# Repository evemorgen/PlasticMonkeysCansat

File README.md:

# Welcome to Plastic Monkeys - Emergency Beacan repo

This is the place where we keep all our work related to Emergency Beacan project.

We are building a CanSat (CanSat is a small soda-sized piece of electronics, created to conduct a scientific mission) equiped with multiple sensors, radio, GPS, thermal camera and screen to provide communication to the victims of natural disasters. Usually, after an earthquake or tsunami, big expeditions and rescue operations take place. Unfortunately they are very often dangerous for rescuers and very expensive. We came up with a solution - instead of people, we can send there many small sats, anyone who finds them can easily send their localization to the rescue center and have a short interview. 

----

## Repo structure

Emergency Beacan is multidisciplinary project involving software, electronics, mechanical design and so on. That being said, there are couple directories covering all mentioned before:

  - [`code`](code/) - keeps all software related stuff
  - [`docs`](docs/) - is the place where we keep project documentation, you might be espetialy interested in our [reports](docs/reports)
  - [`assets`](assets/) - contains all graphical designs regarding our logos and .. assets?
  - [`diagrams`](diagrams/) - all things related to visual representation of conceptual design

----

## Where to find us

We are present in most of modern social media platforms, you can follow us at:
  - our website <http://plastic-monkeys.space>
  - [facebook](https://www.facebook.com/pmcansat/)
  - [instagram](https://www.instagram.com/pmcansat/)
  - [youtube](https://www.youtube.com/channel/UCQk3wuW7xEt5WVLtaiRNTGQ)
  - or write us old fashioned email <hello@plastic-monkeys.space>

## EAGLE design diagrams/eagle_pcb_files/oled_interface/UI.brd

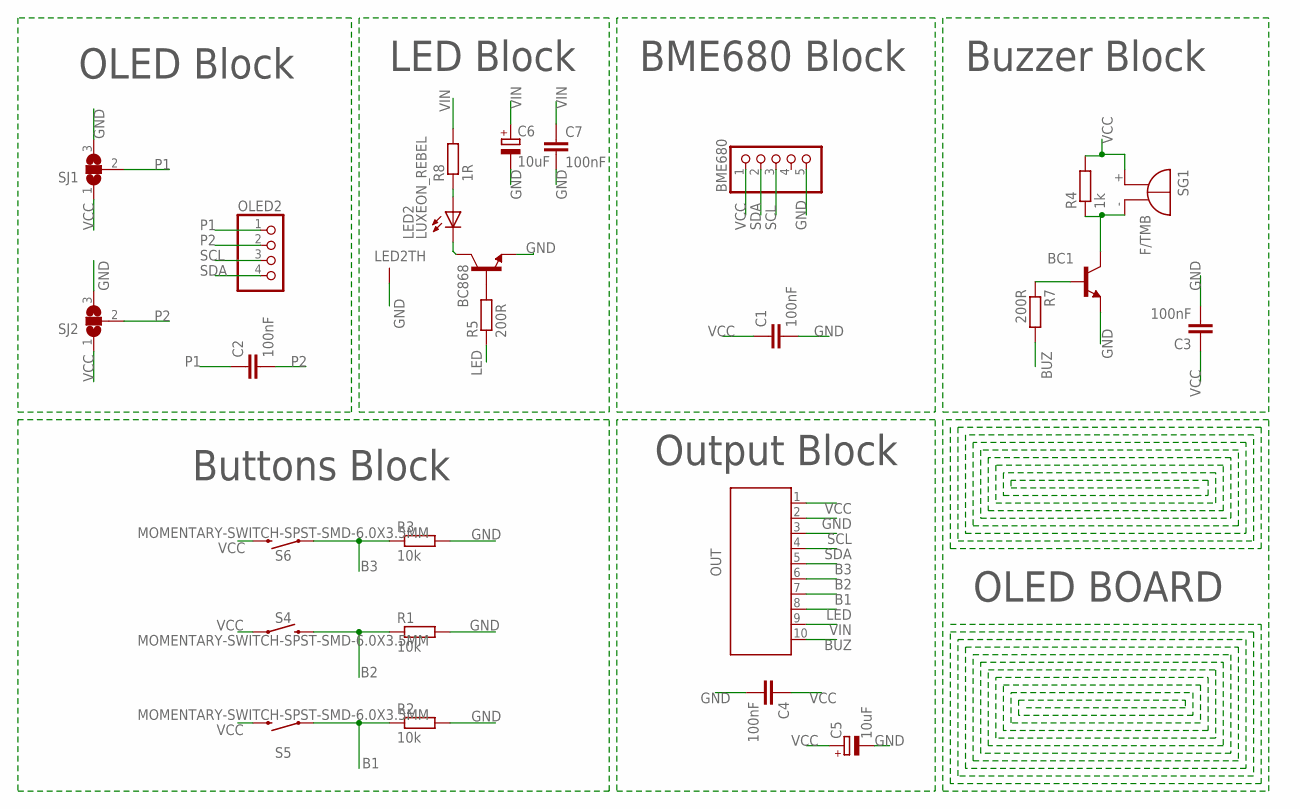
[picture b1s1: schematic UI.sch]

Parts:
BC1, BC868: BC868-NPN-SOT89-BCE; SOT89-BCE
BME680: PINHD-1X5; 1X05
C1, C2, C3, C7: 100nF; C0805
C4: 100nF; C1808
C5, C6: 10uF; SMC_A
LED2: LUXEON_REBEL
OLED2: PINHD-1X4; 1X04
OUT: 686110183422
R1, R2, R3: 10k; M1206
R4: 1k; M0805
R5, R7: 200R; M0805
R8: 1R; R3216
S4, S5, S6: MOMENTARY-SWITCH-SPST-SMD-6.0X3.5MM; TACTILE_SWITCH_SMD_6.0X3.5MM
SG1: F/TMB
SJ1, SJ2: SJ2W; SJ_2

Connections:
B1: OUT.7 (4), R2.1, S5.1
B2: OUT.6 (5), R1.1, S4.2
B3: OUT.5 (6), R3.1, S6.1
BUZ: OUT.10 (1), R7.2
GND: BC1.E, BC868.E, BME680.5, C1.2, C3.2, C4.2, C5.-, C6.-, C7.2, LED2.TH, LED2.TH@1 (TH), LED2.TH@2 (TH), LED2.TH@3 (TH), LED2.TH@4 (TH), OUT.2 (9), R1.2, R2.2, R3.2, SJ1.3, SJ2.3
LED: OUT.8 (3), R5.1
unnamed: LED2.A, LED2.A@1 (A), R8.1
unnamed: BC868.C, LED2.C, LED2.C@1 (C)
unnamed: BC868.B, R5.2
unnamed: BC1.B, R7.1
unnamed: BC1.C, R4.1, SG1.-
P1: C2.1, OLED2.1, SJ1.2
P2: C2.2, OLED2.2, SJ2.2
SCL: BME680.3, OLED2.3, OUT.3 (8)
SDA: BME680.2, OLED2.4, OUT.4 (7)
VCC: BME680.1, C1.1, C3.1, C4.1, C5.+, OUT.1 (10), R4.2, S4.1, S5.2, S6.2, SG1.+, SJ1.1, SJ2.1
VIN: C6.+, C7.1, OUT.9 (2), R8.2

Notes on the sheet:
OLED Block
LED Block
Buttons Block
BME680 Block
Output Block
Buzzer Block
OLED BOARD

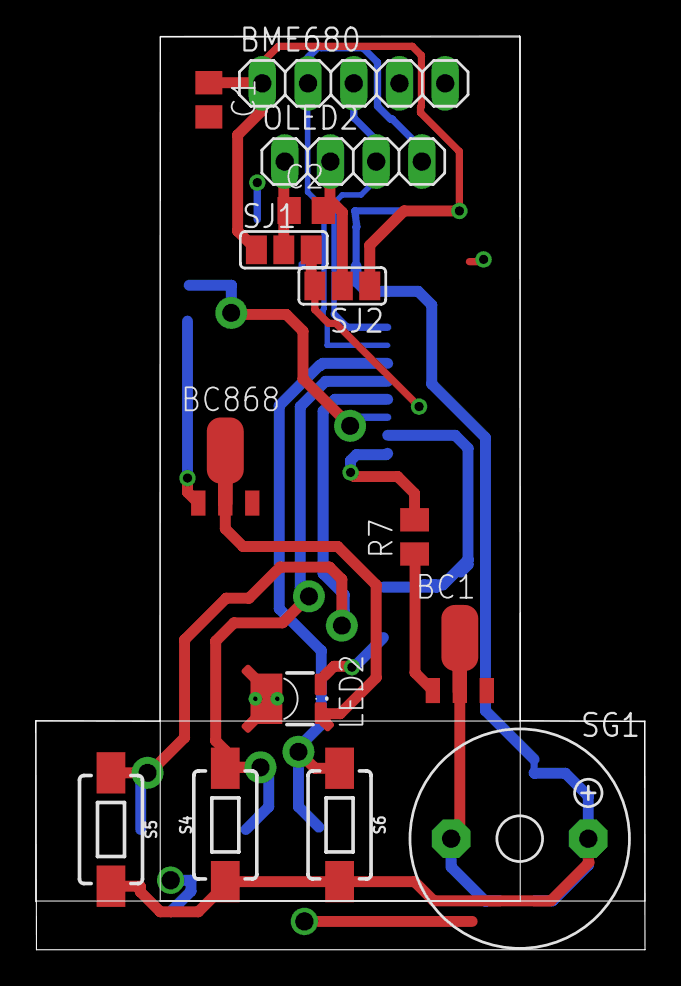
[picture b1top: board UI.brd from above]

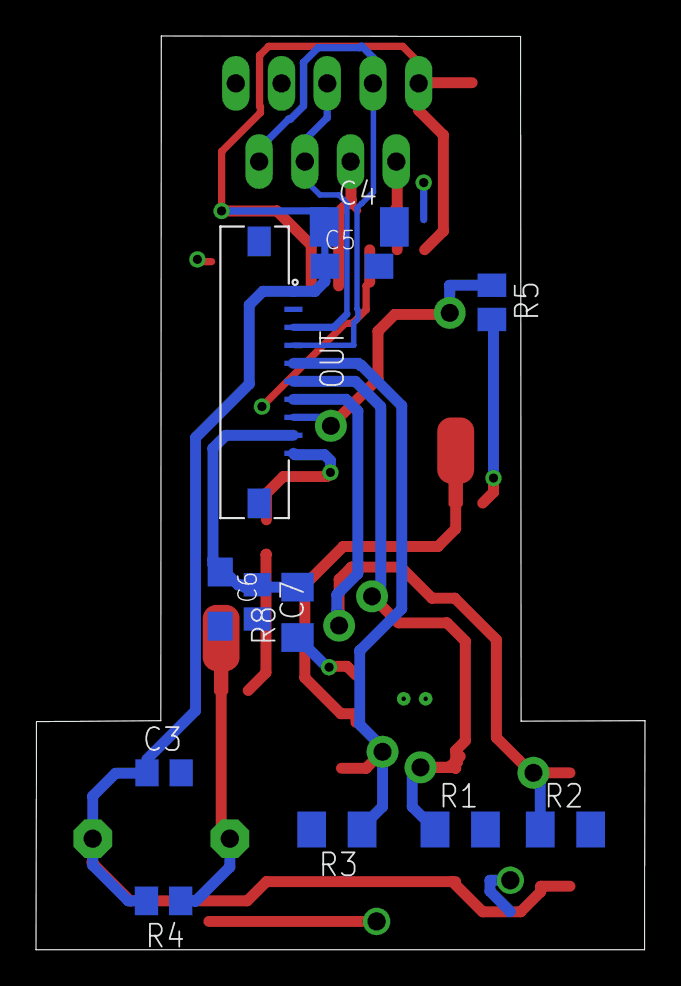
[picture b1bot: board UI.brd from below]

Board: 2 copper layers, 33.8 x 50.8 mm, 26 parts (12 on the bottom side), 17 nets.

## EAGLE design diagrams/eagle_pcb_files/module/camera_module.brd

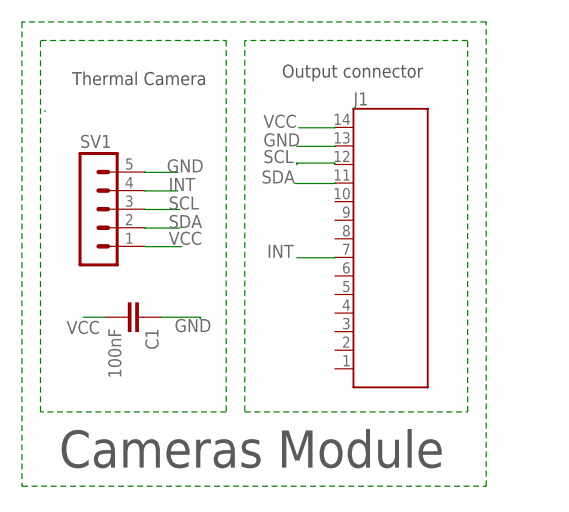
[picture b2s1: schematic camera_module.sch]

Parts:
C1: 100nF; C0805
J1: 686114183522
SV1: MA05-1

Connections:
GND: C1.1, J1.13 (2), SV1.5
INT: J1.7 (8), SV1.4
SCL: J1.12 (3), SV1.3
SDA: J1.11 (4), SV1.2
VCC: C1.2, J1.14 (1), SV1.1

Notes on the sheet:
Thermal Camera
Output connector
Cameras Module

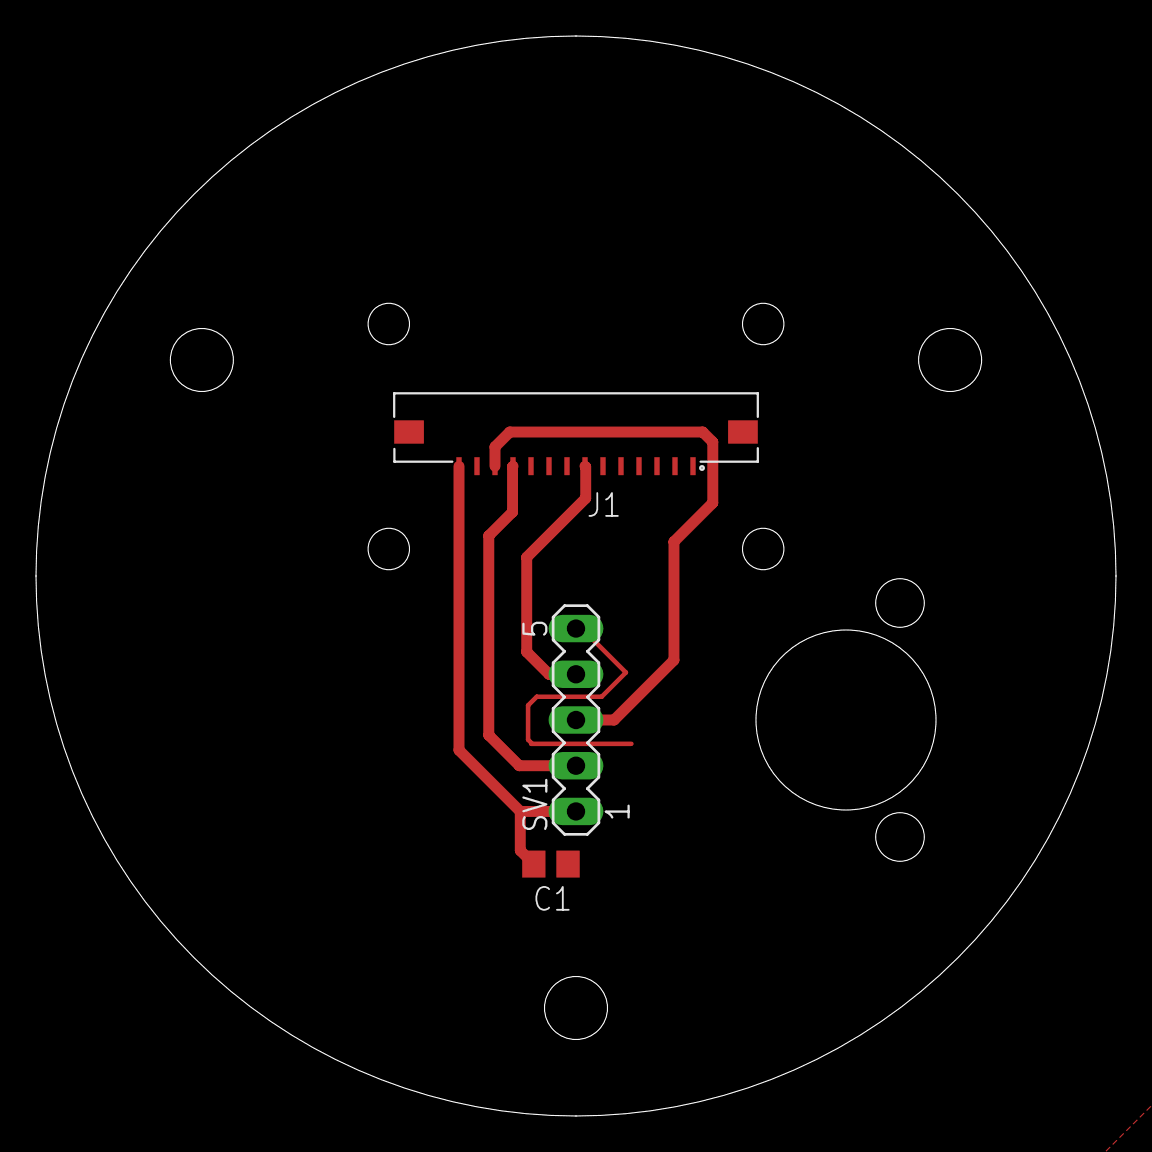
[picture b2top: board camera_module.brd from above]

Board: 2 copper layers, 60.0 x 60.0 mm, 3 parts (0 on the bottom side), 5 nets.

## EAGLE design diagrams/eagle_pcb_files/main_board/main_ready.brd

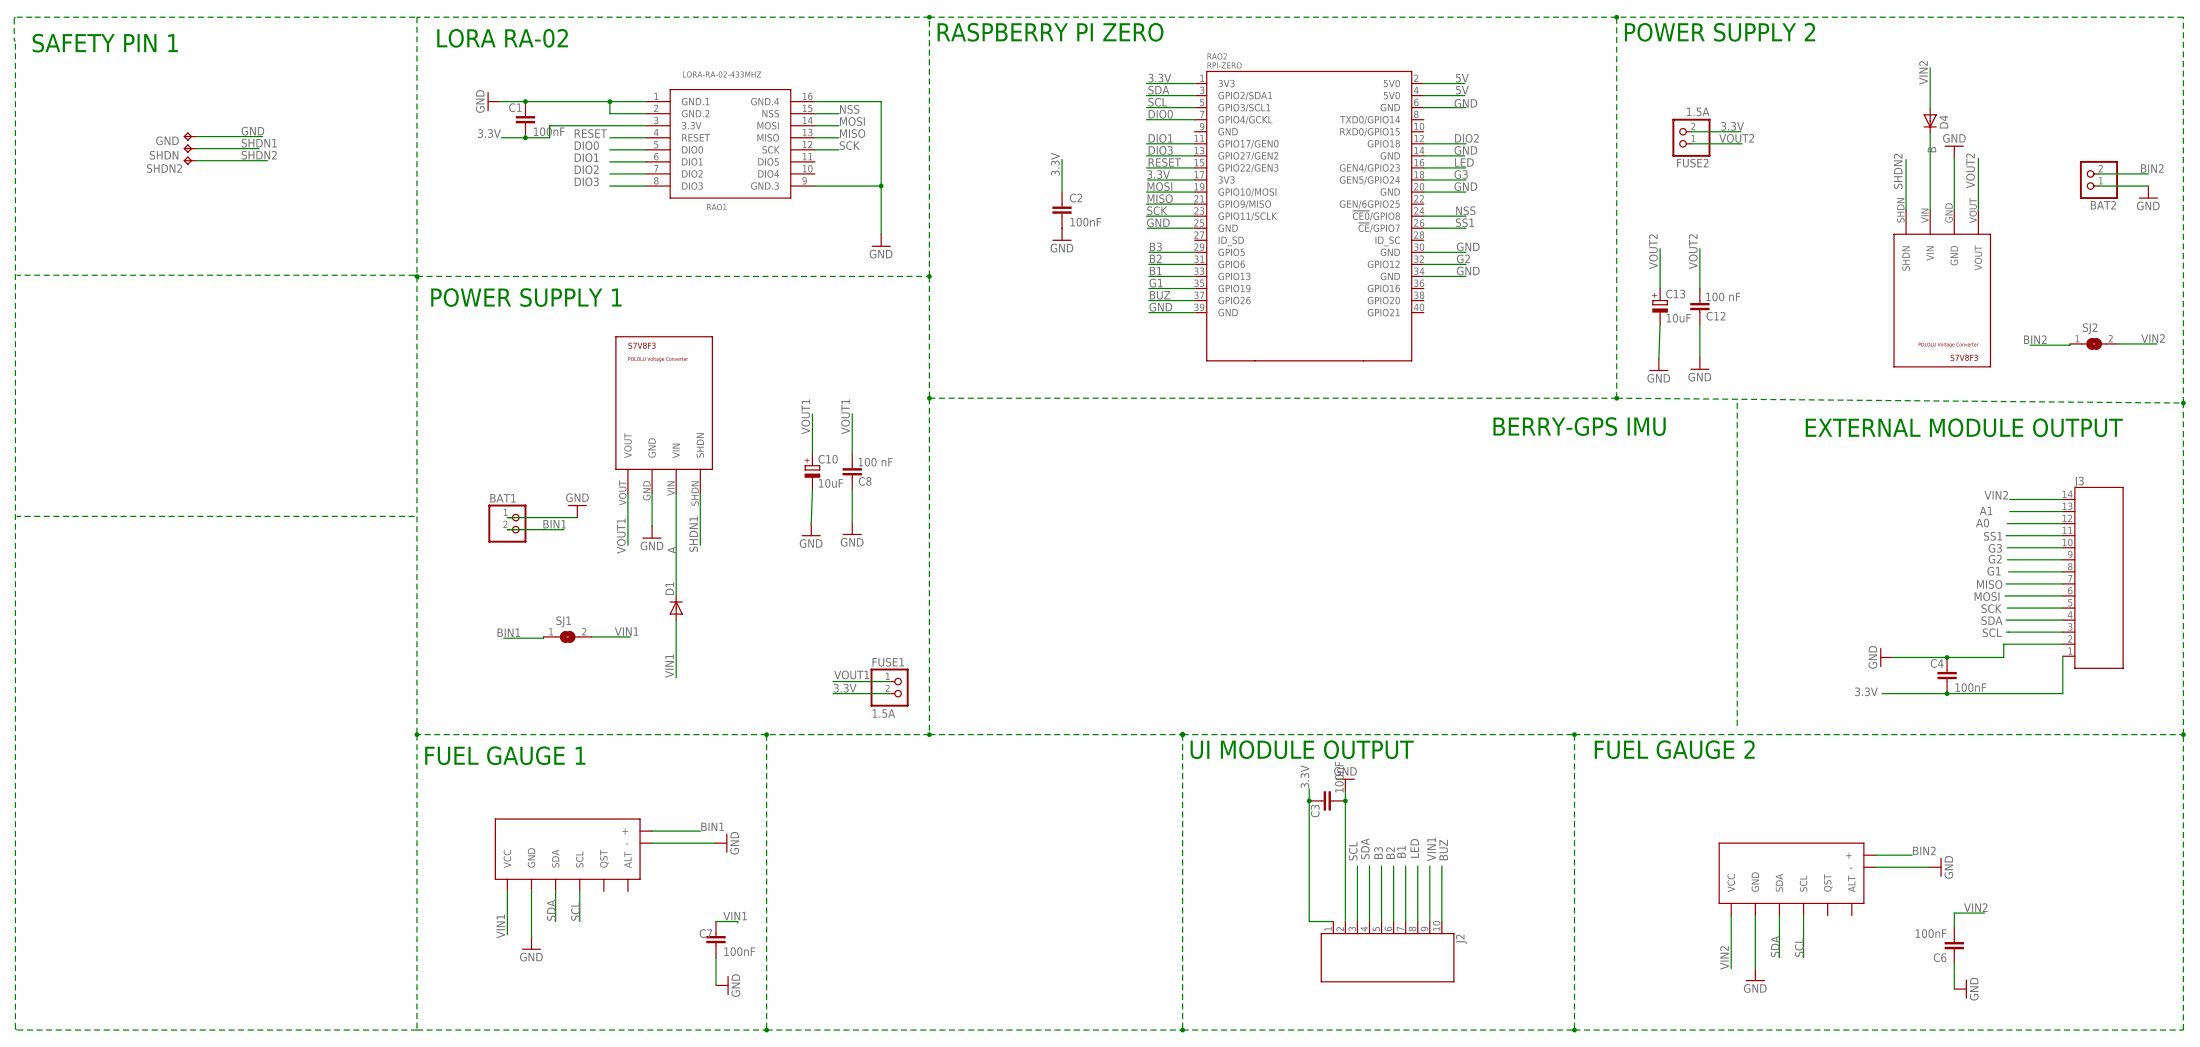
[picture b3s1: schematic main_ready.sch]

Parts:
BAT1, BAT2: PINHD-1X2; 1X02
C1, C2, C3, C4, C6, C7: 100nF; C0805
C8, C12: 100 nF; C0805
C10, C13: 10uF; SMC_A
D1, D4: CGRM4001-G; SOD-123_MINI-SMA
FUSE1, FUSE2: 1.5A; 1X02
GND: TPTP19R; TP19R
J2: 686110183522
J3: 686114183522
RAO1: LORA-RA-02-433MHZ; LORA-RA2-SMD
RAO2: RPI-ZERO; RASPBERRYPI_BASTELSTUBE_V13_RASPI_BOARD_B+_FULL
RAO3, RAO4: S7V8F3
SHDN: TPTP19R; TP19R
SHDN2: TPTP20R; TP20R
SJ1, SJ2: SJW
U$3, U$9: POLOLU_FUEL_GAUGEBREAKBOARD; BREAKBOARD

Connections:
3.3V: C1.2, C2.1, C3.1, C4.2, FUSE1.2, FUSE2.2, J2.1 (10), J3.1 (14), RAO1.3 (3.3V), RAO2.1 (3V3), RAO2.17 (3V3)
5V: RAO2.2 (5V0), RAO2.4 (5V0)
A: D1.C, RAO3.VIN
A0: J3.12 (3)
A1: J3.13 (2)
B: D4.C, RAO4.VIN
B1: J2.7 (4), RAO2.33 (GPIO13)
B2: J2.6 (5), RAO2.31 (GPIO6)
B3: J2.5 (6), RAO2.29 (GPIO5)
BIN1: BAT1.2, SJ1.1, U$3.+
BIN2: BAT2.2, SJ2.1, U$9.+
BUZ: J2.10 (1), RAO2.37 (GPIO26)
DIO0: RAO1.5 (DIO0), RAO2.7 (GPIO4/GCKL)
DIO1: RAO1.6 (DIO1), RAO2.11 (GPIO17/GEN0)
DIO2: RAO1.7 (DIO2), RAO2.12 (GPIO18)
DIO3: RAO1.8 (DIO3), RAO2.13 (GPIO27/GEN2)
G1: J3.8 (7), RAO2.35 (GPIO19)
G2: J3.9 (6), RAO2.32 (GPIO12)
G3: J3.10 (5), RAO2.18 (GEN5/GPIO24)
GND: BAT1.1, BAT2.1, C1.1, C2.2, C3.2, C4.1, C6.1, C7.2, C8.2, C10.-, C12.2, C13.-, GND.TP, J2.2 (9), J3.2 (13), RAO1.1 (GND.1), RAO1.2 (GND.2), RAO1.9 (GND.3), RAO1.16 (GND.4), RAO2.6 (GND), RAO2.14 (GND), RAO2.20 (GND), RAO2.25 (GND), RAO2.30 (GND), RAO2.34 (GND), RAO2.39 (GND), RAO3.GND, RAO4.GND, U$3.-, U$3.GND, U$9.-, U$9.GND
LED: J2.8 (3), RAO2.16 (GEN4/GPIO23)
MISO: J3.7 (8), RAO1.13 (MISO), RAO2.21 (GPIO9/MISO)
MOSI: J3.6 (9), RAO1.14 (MOSI), RAO2.19 (GPIO10/MOSI)
NSS: RAO1.15 (NSS), RAO2.24 (!CE0!/GPIO8)
RESET: RAO1.4 (RESET), RAO2.15 (GPIO22/GEN3)
SCK: J3.5 (10), RAO1.12 (SCK), RAO2.23 (GPIO11/SCLK)
SCL: J2.3 (8), J3.3 (12), RAO2.5 (GPIO3/SCL1), U$3.SCL, U$9.SCL
SDA: J2.4 (7), J3.4 (11), RAO2.3 (GPIO2/SDA1), U$3.SDA, U$9.SDA
SHDN1: RAO3.SHDN, SHDN.TP
SHDN2: RAO4.SHDN, SHDN2.TP
SS1: J3.11 (4), RAO2.26 (!CE!/GPIO7)
VIN1: C7.1, D1.A, J2.9 (2), SJ1.2, U$3.VCC
VIN2: C6.2, D4.A, J3.14 (1), SJ2.2, U$9.VCC
VOUT1: C8.1, C10.+, FUSE1.1, RAO3.VOUT
VOUT2: C12.1, C13.+, FUSE2.1, RAO4.VOUT

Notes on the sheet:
LORA RA-02
POWER SUPPLY 1
EXTERNAL MODULE OUTPUT
UI MODULE OUTPUT
FUEL GAUGE 2
POWER SUPPLY 2
RASPBERRY PI ZERO
FUEL GAUGE 1
SAFETY PIN 1
BERRY-GPS IMU

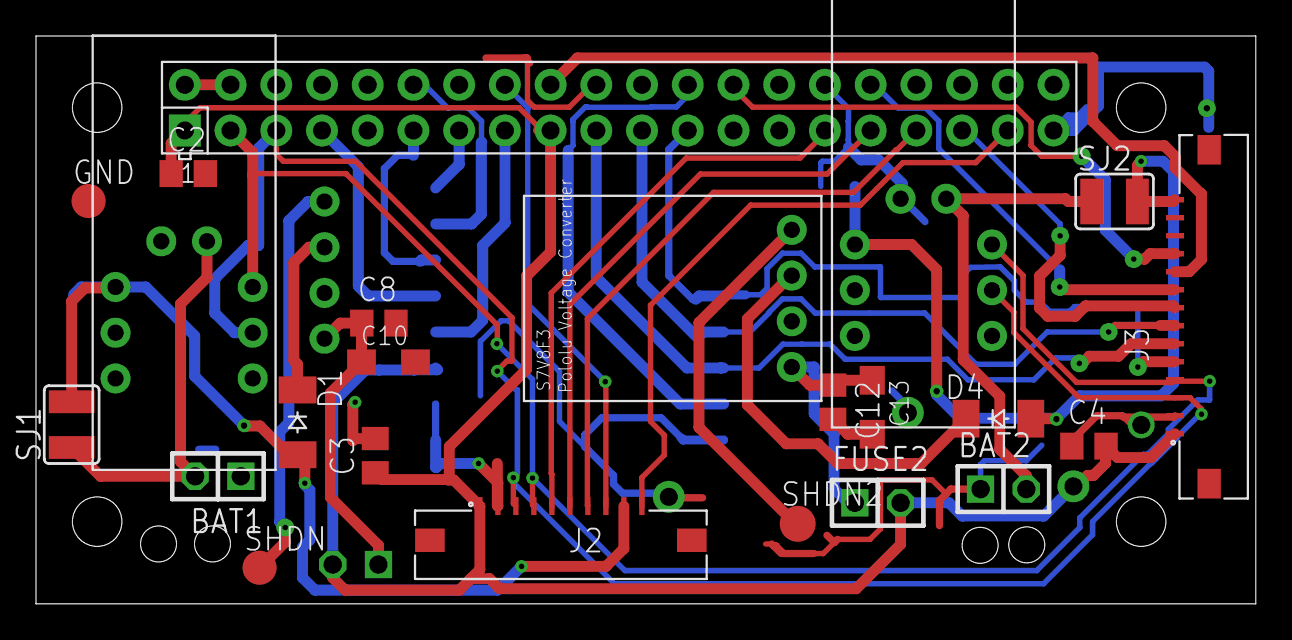
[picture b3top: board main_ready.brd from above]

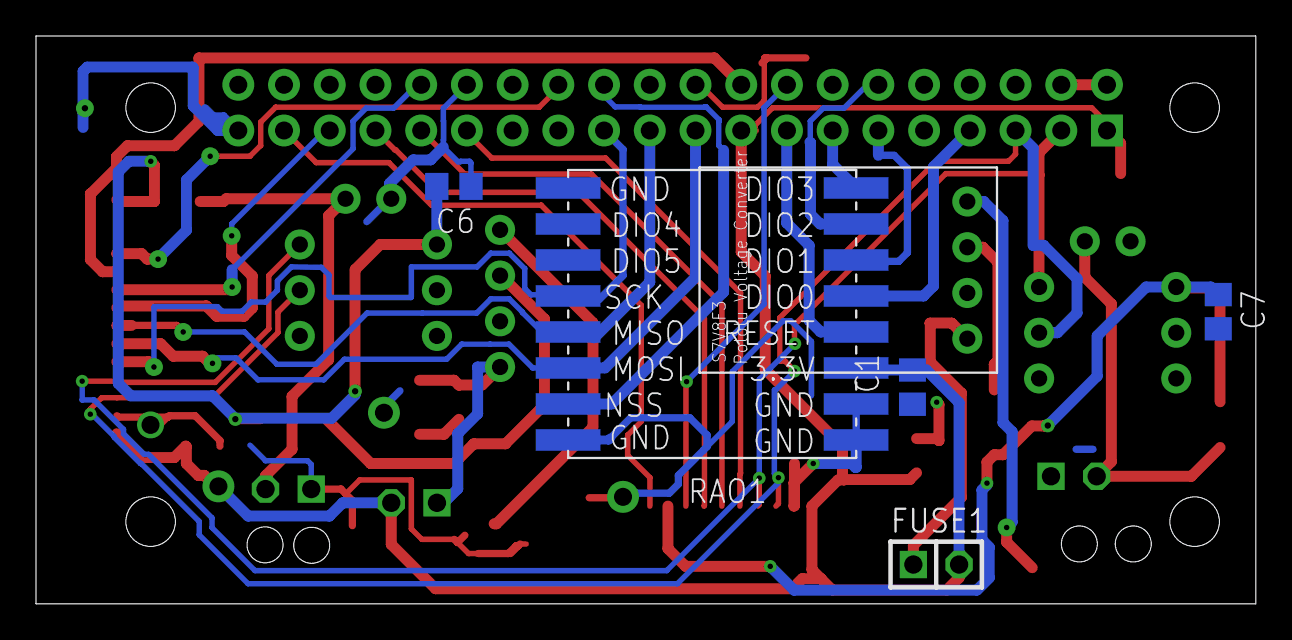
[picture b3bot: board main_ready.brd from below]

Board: 2 copper layers, 67.8 x 31.5 mm, 29 parts (6 on the bottom side), 33 nets.

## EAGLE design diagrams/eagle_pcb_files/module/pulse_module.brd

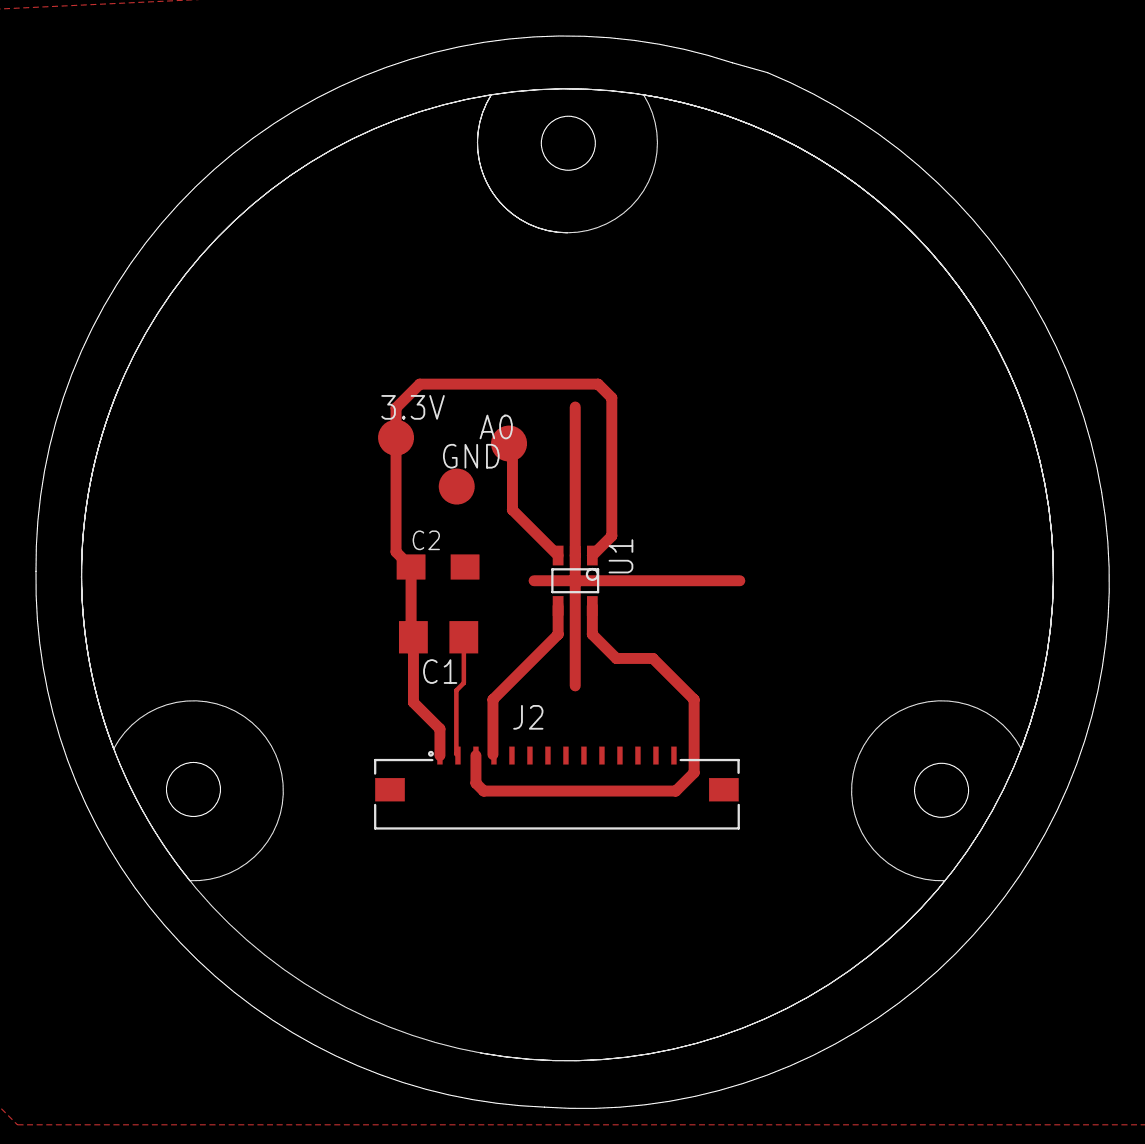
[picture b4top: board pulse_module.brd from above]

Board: 2 copper layers, 59.6 x 59.6 mm, 7 parts (0 on the bottom side), 5 nets.

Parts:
3.3V: TPTP20R; TP20R
A0: TPTP20R; TP20R
C1: 100nF; C1206
C2: 4.7uF; SMC_A
GND: TPTP20R; TP20R
J2: 686114183522
U1: MCP3021; SOT-23-5

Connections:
3.3V: 3.3V.TP, C1.2, C2.+, J2.1, U1.1
AIN: A0.TP, U1.3
GND: C1.1, C2.-, GND.TP, J2.2, U1.2
SCL: J2.3, U1.5
SDA: J2.4, U1.4

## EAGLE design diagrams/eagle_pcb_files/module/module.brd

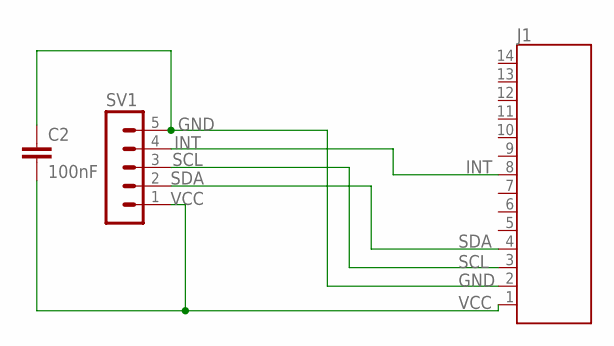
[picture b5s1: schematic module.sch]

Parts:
C2: 100nF; C1206
J1: 686114183522
SV1: MA05-1

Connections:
GND: C2.1, J1.2 (13), SV1.5
INT: J1.8 (7), SV1.4
SCL: J1.3 (12), SV1.3
SDA: J1.4 (11), SV1.2
VCC: C2.2, J1.1 (14), SV1.1

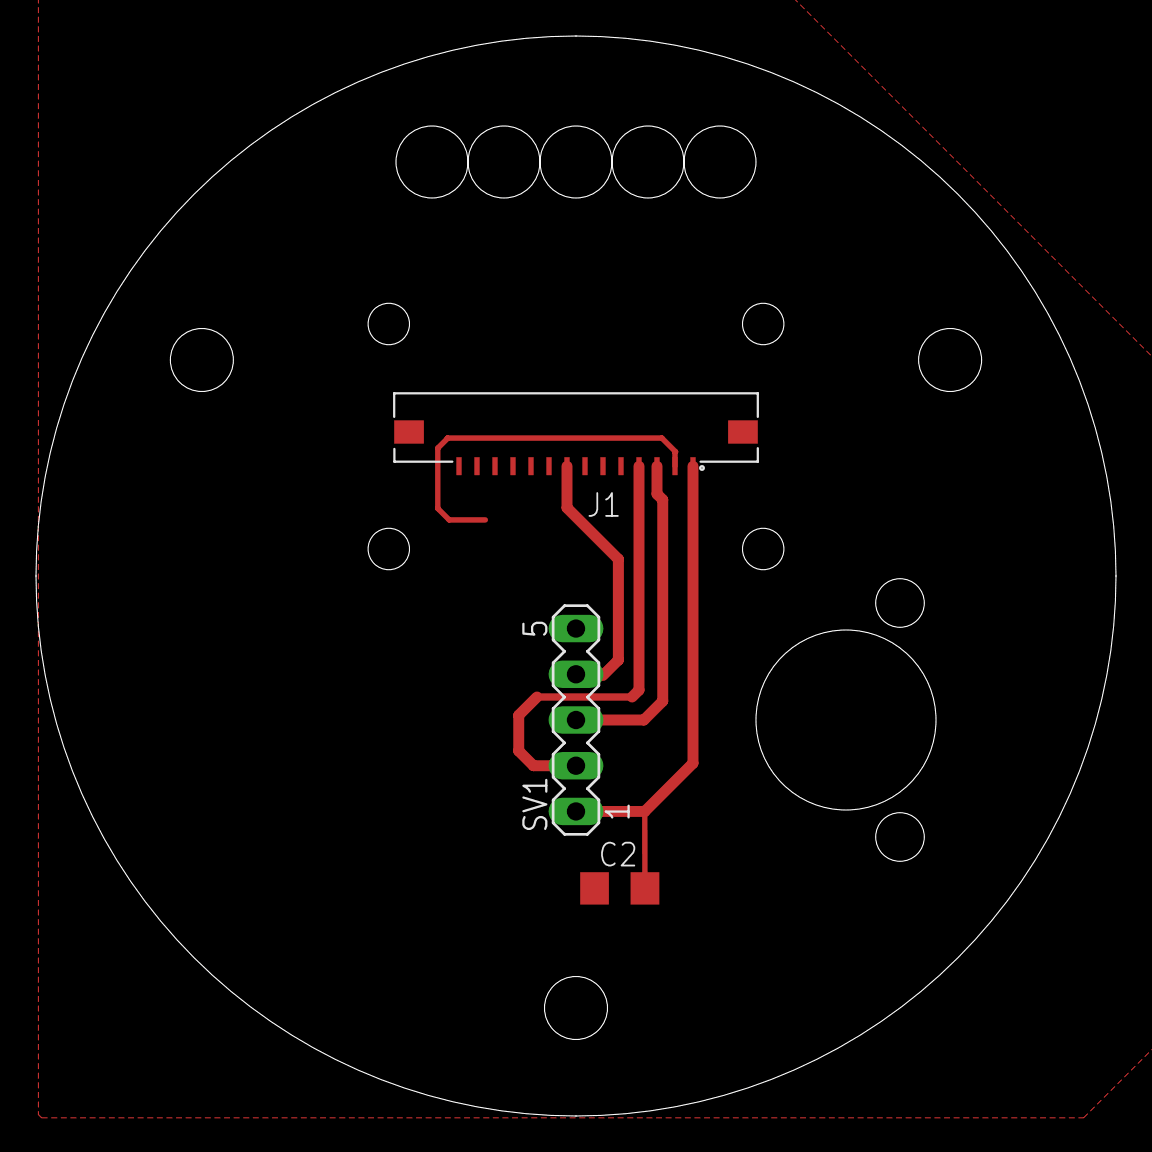
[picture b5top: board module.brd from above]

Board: 2 copper layers, 60.0 x 60.0 mm, 3 parts (0 on the bottom side), 5 nets.

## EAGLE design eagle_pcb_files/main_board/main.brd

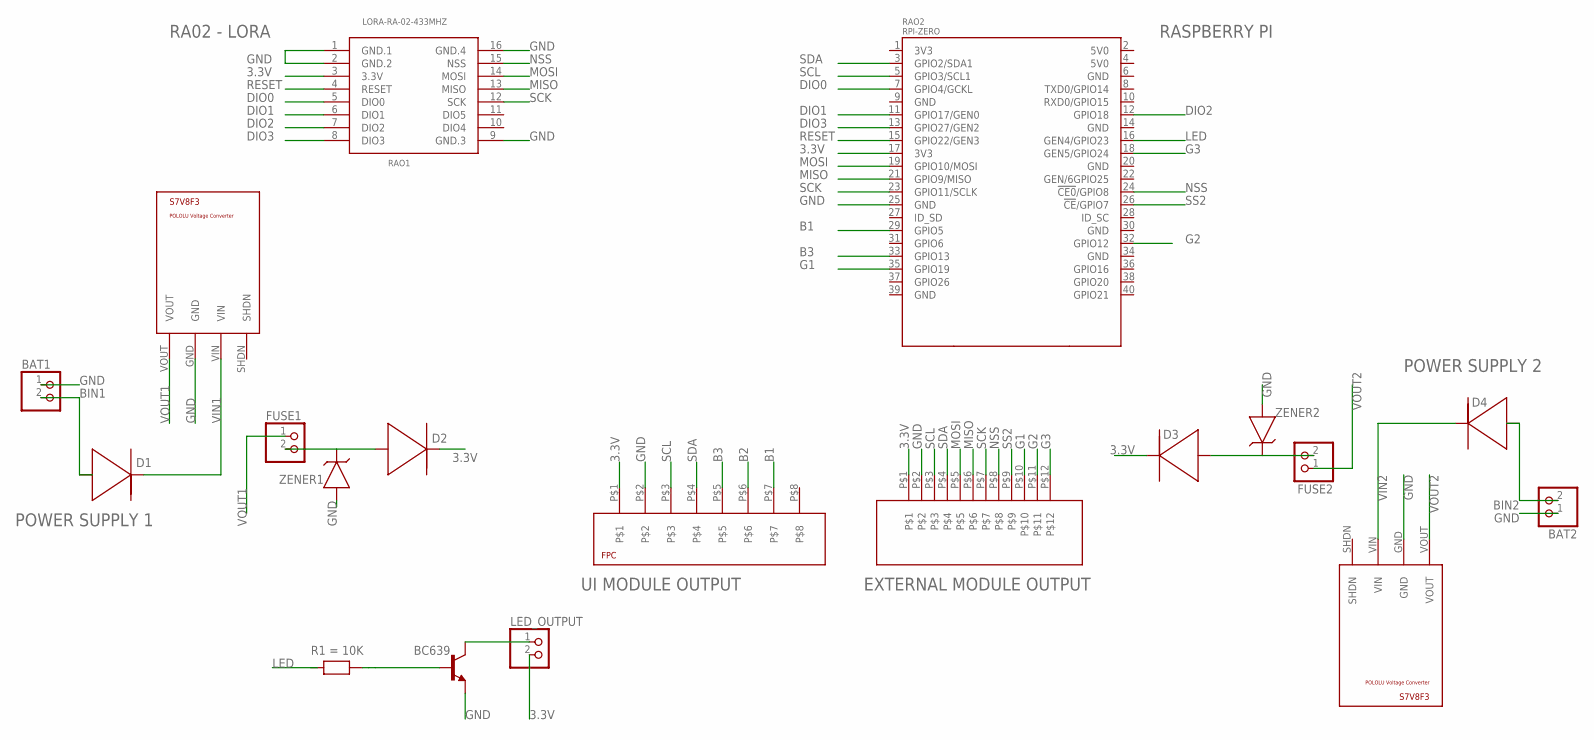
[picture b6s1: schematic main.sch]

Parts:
BAT1, BAT2: PINHD-1X2; 1X02
BC639: BCX59SMD; TO92-EBC
D1: DIODE1206; 1206
FUSE1, FUSE2: PINHD-1X2; 1X02
LED_OUTPUT: PINHD-1X2; 1X02
R1: RESISTOR1206; 1206
RAO1: LORA-RA-02-433MHZ; LORA-RA2-SMD
RAO2: RPI-ZERO; RASPBERRYPI_BASTELSTUBE_V13_RASPI_BOARD_B+_FULL
RAO3, RAO4: S7V8F3
U$1: TYCO_8PIN_1MM_SMD; TYCO_1MM_8PIN
U$2: TYCO_12PIN_1MM_SMD; TYCO_1MM_12PIN
U$4, U$7, U$8: DIODE1206; 1206
U$5, U$6: SMD_COMPONENT1206; 1206

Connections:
3.3V: LED_OUTPUT.2, RAO1.3 (3.3V), RAO2.17 (3V3), U$1.P$1, U$2.P$1, U$4.P$2, U$7.P$2
B1: RAO2.29 (GPIO5), U$1.P$7
B2: U$1.P$6
B3: RAO2.33 (GPIO13), U$1.P$5
BIN1: BAT1.2, D1.P$1
BIN2: BAT2.2, U$8.P$1
DIO0: RAO1.5 (DIO0), RAO2.7 (GPIO4/GCKL)
DIO1: RAO1.6 (DIO1), RAO2.11 (GPIO17/GEN0)
DIO2: RAO1.7 (DIO2), RAO2.12 (GPIO18)
DIO3: RAO1.8 (DIO3), RAO2.13 (GPIO27/GEN2)
G1: RAO2.35 (GPIO19), U$2.P$10
G2: RAO2.32 (GPIO12), U$2.P$11
G3: RAO2.18 (GEN5/GPIO24), U$2.P$12
GND: BAT1.1, BAT2.1, BC639.E, RAO1.1 (GND.1), RAO1.2 (GND.2), RAO1.9 (GND.3), RAO1.16 (GND.4), RAO2.25 (GND), RAO3.GND, RAO4.GND, U$1.P$2, U$2.P$2, U$5.P$1, U$6.P$1
LED: R1.P$1, RAO2.16 (GEN4/GPIO23)
MISO: RAO1.13 (MISO), RAO2.21 (GPIO9/MISO), U$2.P$6
MOSI: RAO1.14 (MOSI), RAO2.19 (GPIO10/MOSI), U$2.P$5
unnamed: BC639.B, R1.P$2
unnamed: FUSE2.2, U$6.P$2, U$7.P$1
unnamed: FUSE1.2, U$4.P$1, U$5.P$2
unnamed: BC639.C, LED_OUTPUT.1
NSS: RAO1.15 (NSS), RAO2.24 (!CE0!/GPIO8), U$2.P$8
RESET: RAO1.4 (RESET), RAO2.15 (GPIO22/GEN3)
SCK: RAO1.12 (SCK), RAO2.23 (GPIO11/SCLK), U$2.P$7
SCL: RAO2.5 (GPIO3/SCL1), U$1.P$3, U$2.P$3
SDA: RAO2.3 (GPIO2/SDA1), U$1.P$4, U$2.P$4
SS2: RAO2.26 (!CE!/GPIO7), U$2.P$9
VIN1: D1.P$2, RAO3.VIN
VIN2: RAO4.VIN, U$8.P$2
VOUT1: FUSE1.1, RAO3.VOUT
VOUT2: FUSE2.1, RAO4.VOUT

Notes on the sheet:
UI MODULE OUTPUT
POWER SUPPLY 1
POWER SUPPLY 2
RASPBERRY PI
RA02 - LORA
EXTERNAL MODULE OUTPUT

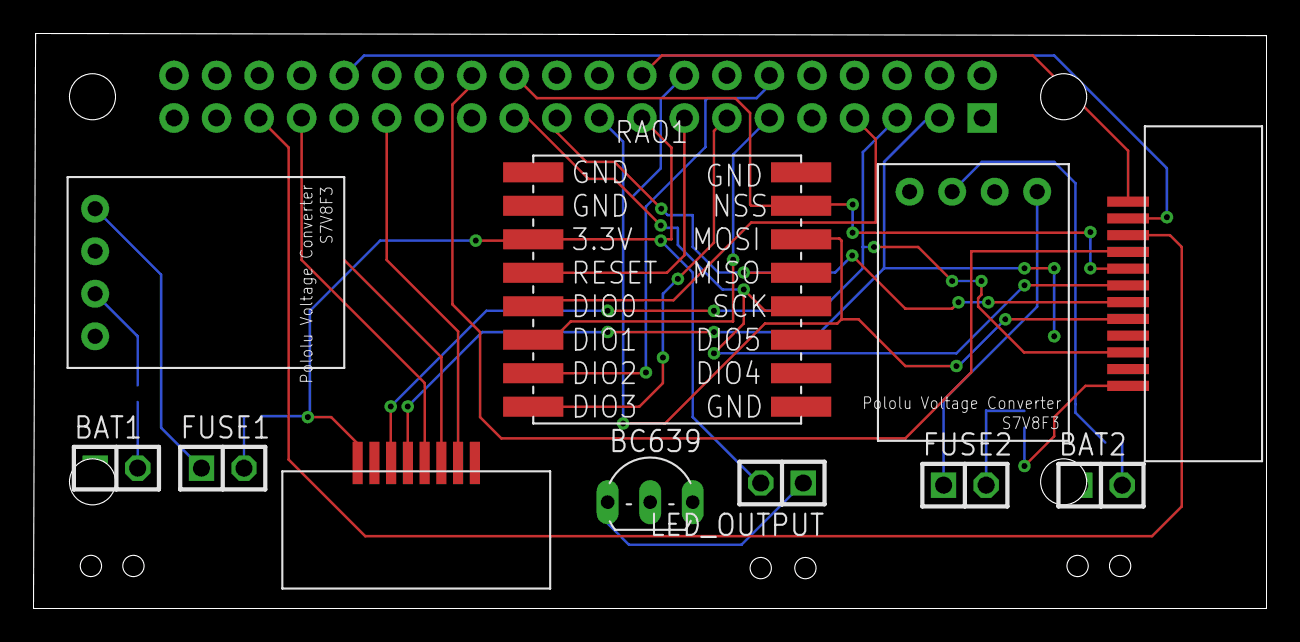
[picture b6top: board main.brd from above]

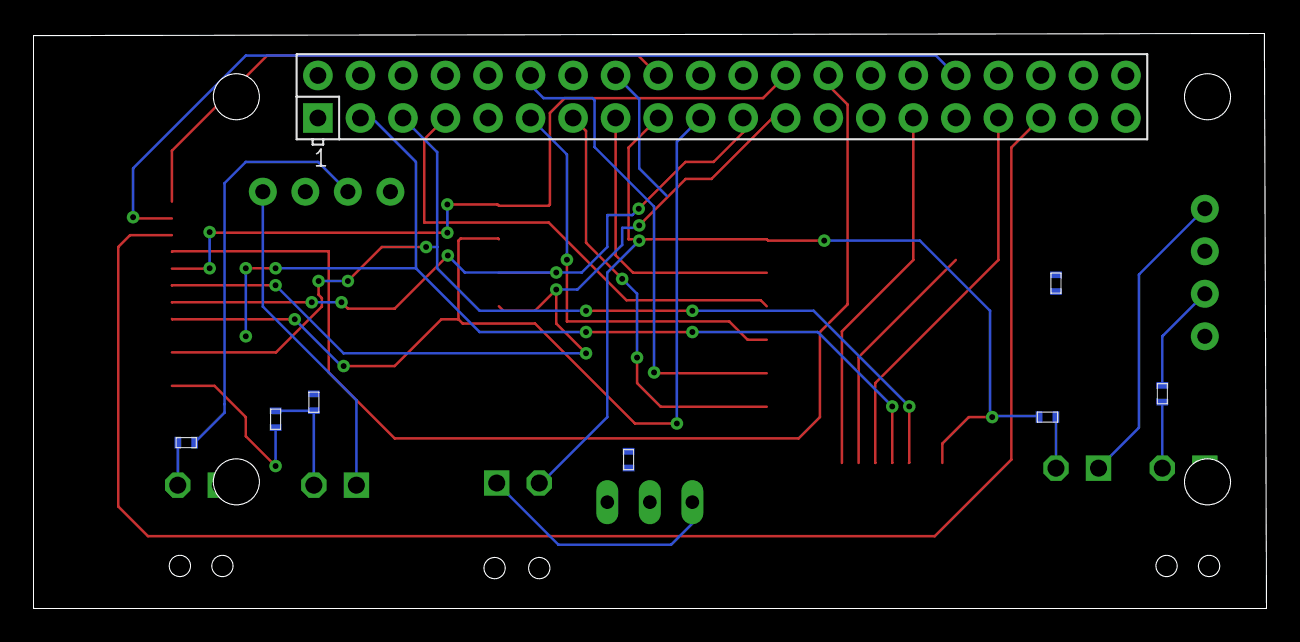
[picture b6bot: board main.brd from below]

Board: 2 copper layers, 73.6 x 34.3 mm, 20 parts (8 on the bottom side), 30 nets.

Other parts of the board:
FRAME2: FRAME-LEDGER; CREATIVE_COMMONS

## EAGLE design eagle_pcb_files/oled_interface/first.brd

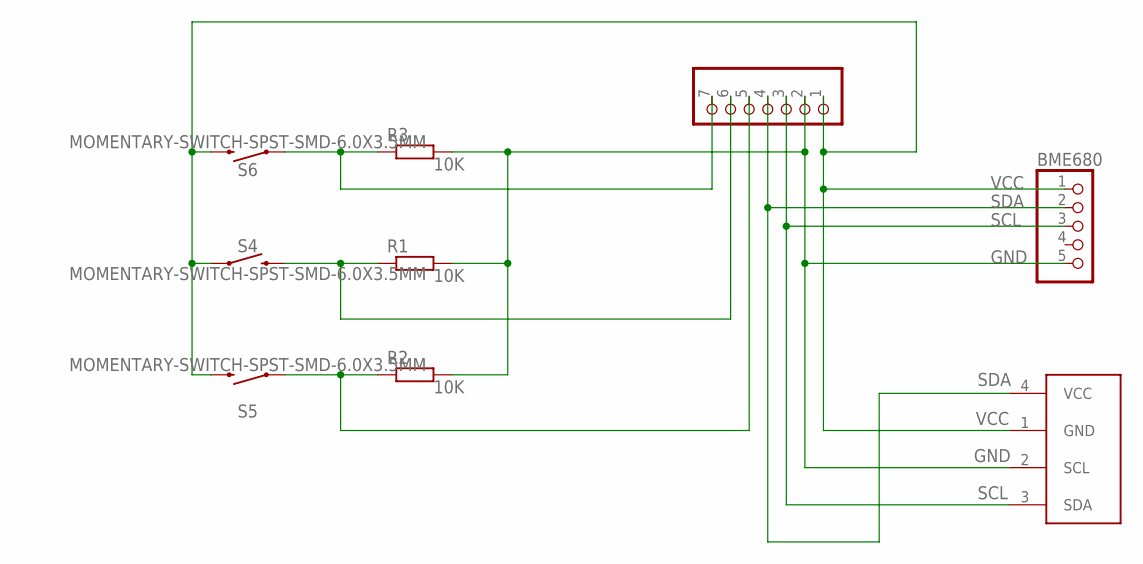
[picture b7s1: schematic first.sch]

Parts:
BME680: PINHD-1X5; 1X05
R1, R2, R3: R-EU_M1206; M1206
S4, S5, S6: MOMENTARY-SWITCH-SPST-SMD-6.0X3.5MM; TACTILE_SWITCH_SMD_6.0X3.5MM
SDA: PINHD-1X7; 1X07
U$1: I2C_OLED; I2C_OLED_PACKAGE

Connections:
B1: R2.1, S5.1, SDA.5
B2: R1.1, S4.2, SDA.6
B3: R3.1, S6.1, SDA.7
GND: BME680.5, R1.2, R2.2, R3.2, SDA.2, U$1.2 (SCL)
unnamed: BME680.2, SDA.4, U$1.4 (VCC)
SCL: BME680.3, SDA.3, U$1.3 (SDA)
VCC: BME680.1, S4.1, S5.2, S6.2, SDA.1, U$1.1 (GND)

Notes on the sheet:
VCC
GND
SCL
SDA

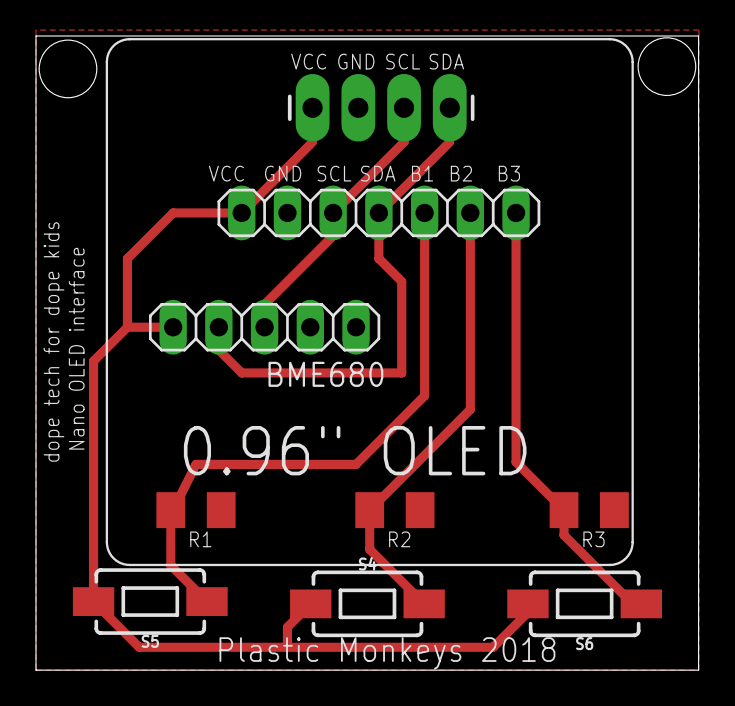
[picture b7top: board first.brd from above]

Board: 2 copper layers, 36.8 x 35.2 mm, 9 parts (0 on the bottom side), 7 nets.

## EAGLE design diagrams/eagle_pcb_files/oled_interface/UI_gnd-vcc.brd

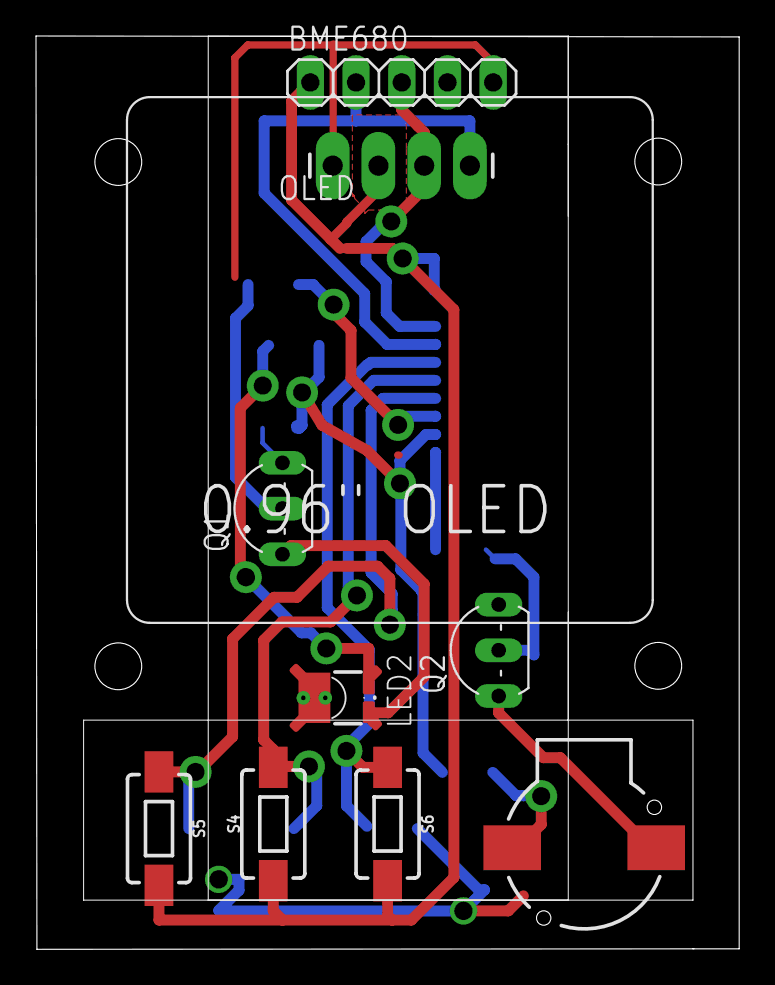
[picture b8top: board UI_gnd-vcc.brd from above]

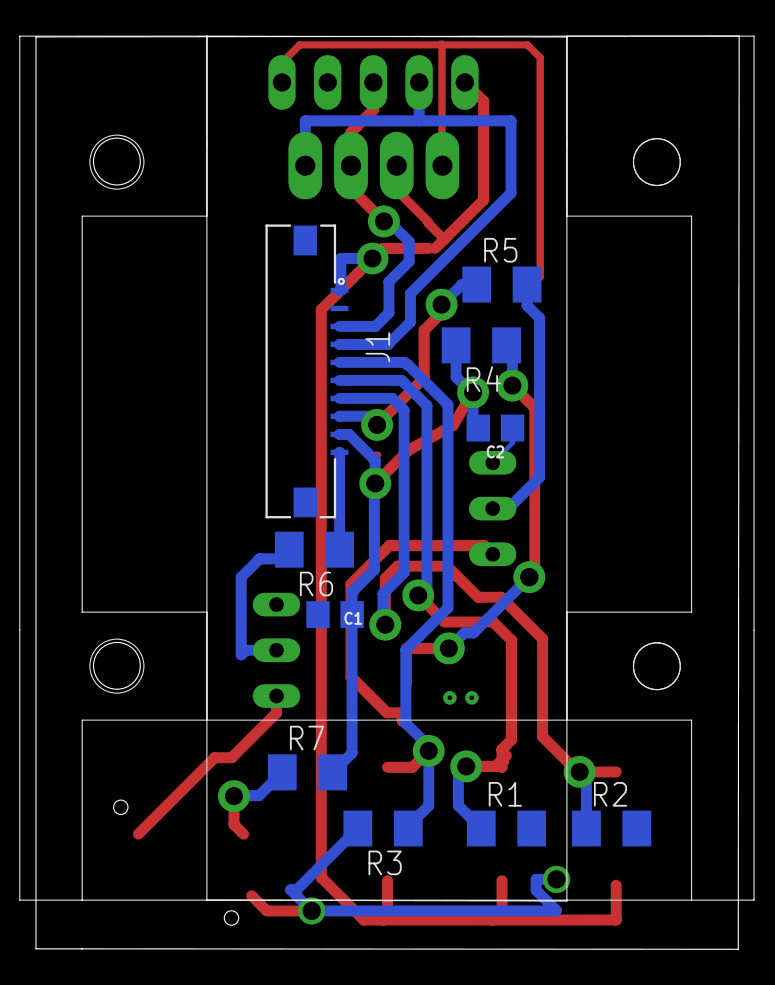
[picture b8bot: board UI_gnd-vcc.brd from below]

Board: 2 copper layers, 39.1 x 50.7 mm, 19 parts (10 on the bottom side), 15 nets.

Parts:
B1: Buzzer; BUZZER-CCV
BME680: 1X05
C1, C2: C0805
J1: 686110183422
LED2: LUXEON_REBEL
OLED: I2C_OLED; I2C_OLED_PACKAGE
Q1, Q2: BCX59SMD; TO92-EBC
R1, R2, R3, R5, R6: 10k; M1206
R4: 10R; M1206
R7: 200R; M1206
S4, S5, S6: MOMENTARY-SWITCH-SPST-SMD-6.0X3.5MM; TACTILE_SWITCH_SMD_6.0X3.5MM

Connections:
B1: J1.7, R2.1, S5.1
B2: J1.6, R1.1, S4.2
B3: J1.5, R3.1, S6.1
BUZ: J1.10, R6.1
GND: BME680.5, C1.1, C2.1, J1.2, OLED.2, Q1.E, Q2.E, R1.2, R2.2, R3.2
LED: J1.8, R5.1
unnamed: LED2.A, LED2.A@1, R4.1
unnamed: LED2.C, LED2.C@1, Q1.C
unnamed: Q1.B, R5.2
unnamed: Q2.B, R6.2
SCL: BME680.3, J1.3, OLED.3
SDA: BME680.2, J1.4, OLED.4
TH: LED2.TH, LED2.TH@1, LED2.TH@2, LED2.TH@3, LED2.TH@4
VCC: BME680.1, J1.1, S4.1, S5.2, S6.2
VIN1: C1.2, C2.2, J1.9, R4.2, R7.2

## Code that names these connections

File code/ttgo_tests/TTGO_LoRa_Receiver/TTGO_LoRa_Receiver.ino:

#include <LoRa.h>
#include <SPI.h>
#include <Wire.h>  
#include "SSD1306.h" 

#define SCK     5    // GPIO5  -- SX1278's SCK
#define MISO    19   // GPIO19 -- SX1278's MISO
#define MOSI    27   // GPIO27 -- SX1278's MOSI
#define SS      18   // GPIO18 -- SX1278's CS
#define RST     14   // GPIO14 -- SX1278's RESET
#define DI0     26   // GPIO26 -- SX1278's IRQ(Interrupt Request)
#define BAND    433E6// 433 MHz Freq

SSD1306 display(0x3c, 4, 15);
String rssi ;
String packSize ;
String packet ;

void displayLoraData(){
  display.clear();
  display.drawString(0 , 15 , "Received "+ packSize + " bytes");
  display.drawStringMaxWidth(0 , 26 , 128, packet);
  display.drawString(0, 0, rssi);  
  display.display();
}

void readPacket(int packetSize) {
  packet ="";
  packSize = String(packetSize,DEC);
  for (int i = 0; i < packetSize; i++) {
    packet += (char) LoRa.read();
  }
  rssi = "RSSI " + String(LoRa.packetRssi(), DEC) ;
  displayLoraData();
}

void setup() {
  pinMode(16,OUTPUT);

  //Reset OLED
  digitalWrite(16, LOW); 
  delay(50); 
  digitalWrite(16, HIGH);

  //Initialize OLED
  display.init(); 
  display.drawString(0, 0, "Display Init OK");

  //Initialize Serial
  Serial.begin(9600);
  while (!Serial);
  Serial.println("Serial Initialization Successful");
  display.drawString(0, 20, "Serial Init OK");

  //Initialize LoRa
  SPI.begin(SCK,MISO,MOSI,SS);
  LoRa.setPins(SS,RST,DI0);  
  if (!LoRa.begin(434E6)) {
    Serial.println("Starting LoRa failed!");
    display.drawString(0, 40, "LoRa Init FAIL");
    display.display();
    while (1);
  }
  LoRa.receive();
  //LoRa.disableCrc();
  Serial.println("Init OK");
  display.drawString(0, 40, "LoRa Init OK");
  display.display();
  
  delay(3000);
}

void loop() {
  int packetSize = LoRa.parsePacket();
  if (packetSize) readPacket(packetSize);
  delay(10);
}

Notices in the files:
parts and their libraries:
Wurth_Elektronik_Electromechanic_FPC_Con: Copyright: Würth Elektronik
Volks73-MicrochipTechnology: Creative Commons Attribution-ShareAlike 3.0 Unported (CC BY-SA 3.0), http://creativecommons.org/licenses/by-sa/3.0/.
SparkFun-Aesthetics: https://creativecommons.org/licenses/by-sa/4.0
